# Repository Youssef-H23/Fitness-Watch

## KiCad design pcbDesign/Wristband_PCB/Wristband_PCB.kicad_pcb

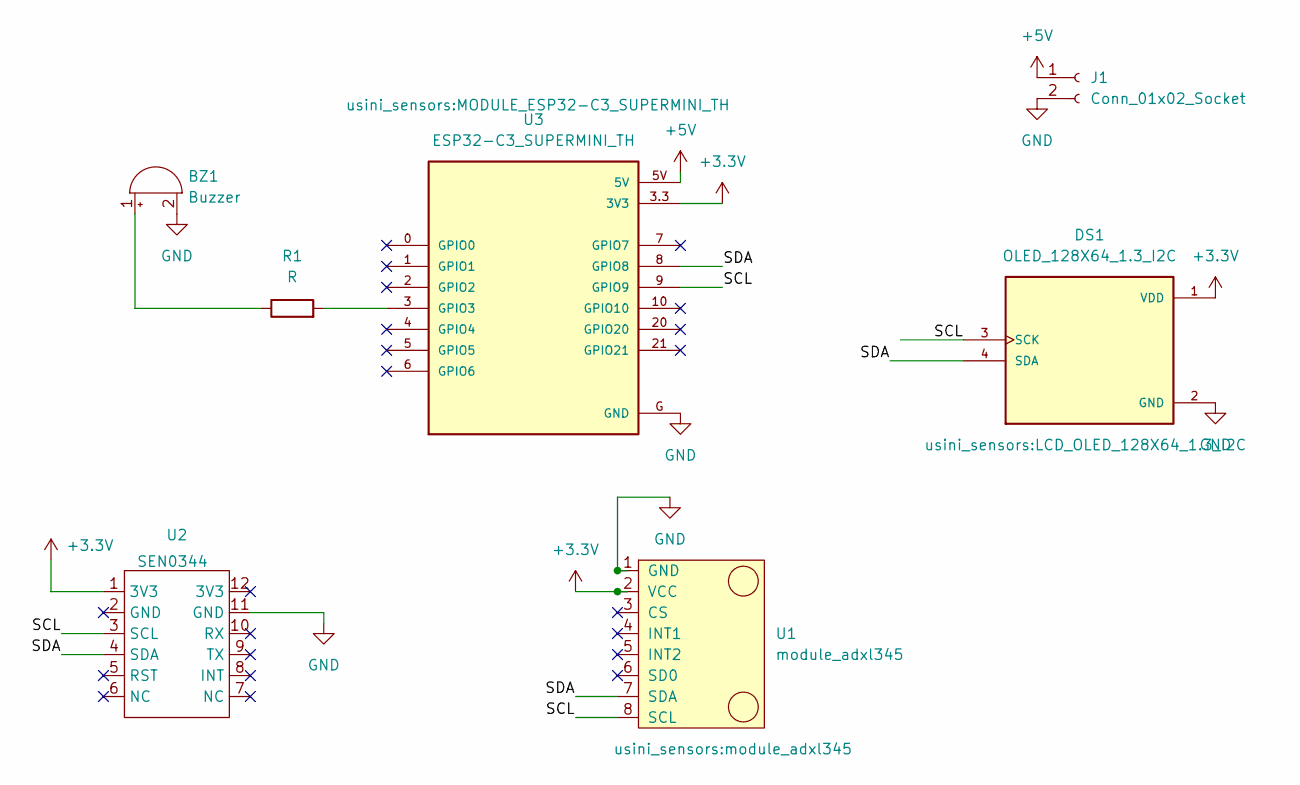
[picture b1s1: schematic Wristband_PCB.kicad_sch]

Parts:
BZ1: Buzzer; Buzzer_12x9.5RM7.6
DS1: OLED_128X64_1.3_I2C; LCD_OLED_128X64_1.3_I2C; PARTREV NA
J1: Conn_01x02_Socket; PinSocket_1x02_P2.54mm_Vertical
R1: R; R_Axial_DIN0204_L3.6mm_D1.6mm_P5.08mm_Horizontal
U1: module_adxl345
U2: SEN0344
U3: ESP32-C3_SUPERMINI_TH; MODULE_ESP32-C3_SUPERMINI_TH

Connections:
+3.3V: DS1.1 (VDD), U1.2 (VCC), U2.1 (3V3), U3.3.3 (3V3)
+5V: J1.1, U3.5V
/SCL: DS1.3 (SCK), U1.8 (SCL), U2.3 (SCL), U3.9 (GPIO9)
/SDA: DS1.4 (SDA), U1.7 (SDA), U2.4 (SDA), U3.8 (GPIO8)
GND: BZ1.2 (-), DS1.2 (GND), J1.2, U1.1 (GND), U2.11 (GND), U3.G (GND)
unnamed: BZ1.1 (+), R1.1
unnamed: R1.2, U3.3 (GPIO3)

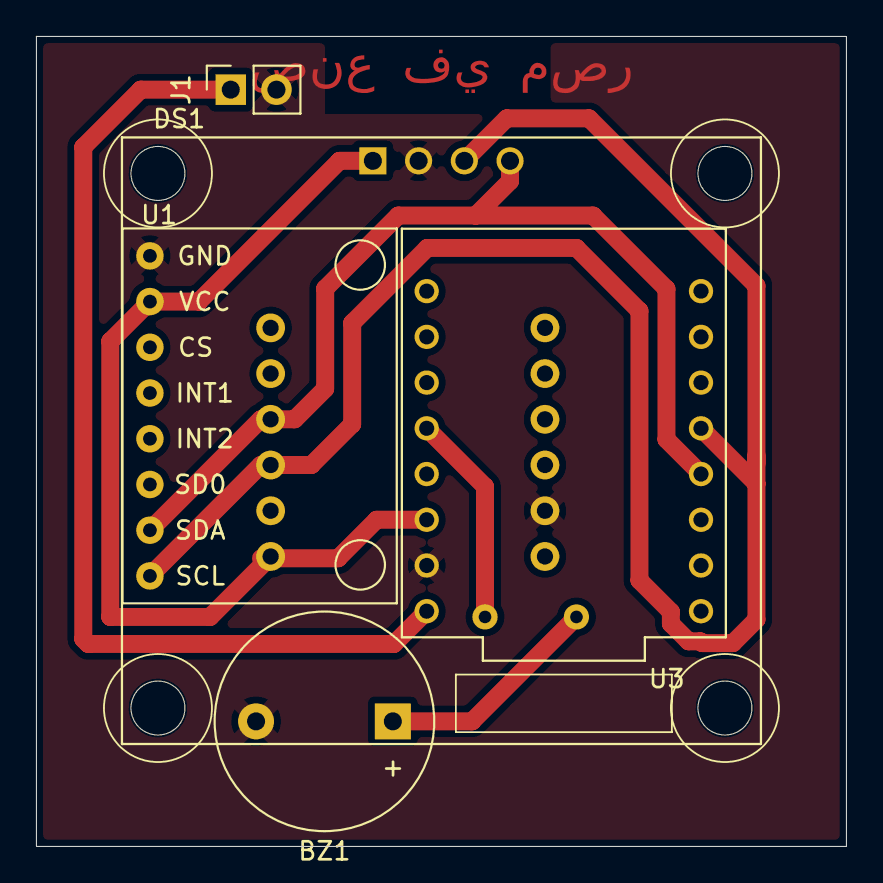
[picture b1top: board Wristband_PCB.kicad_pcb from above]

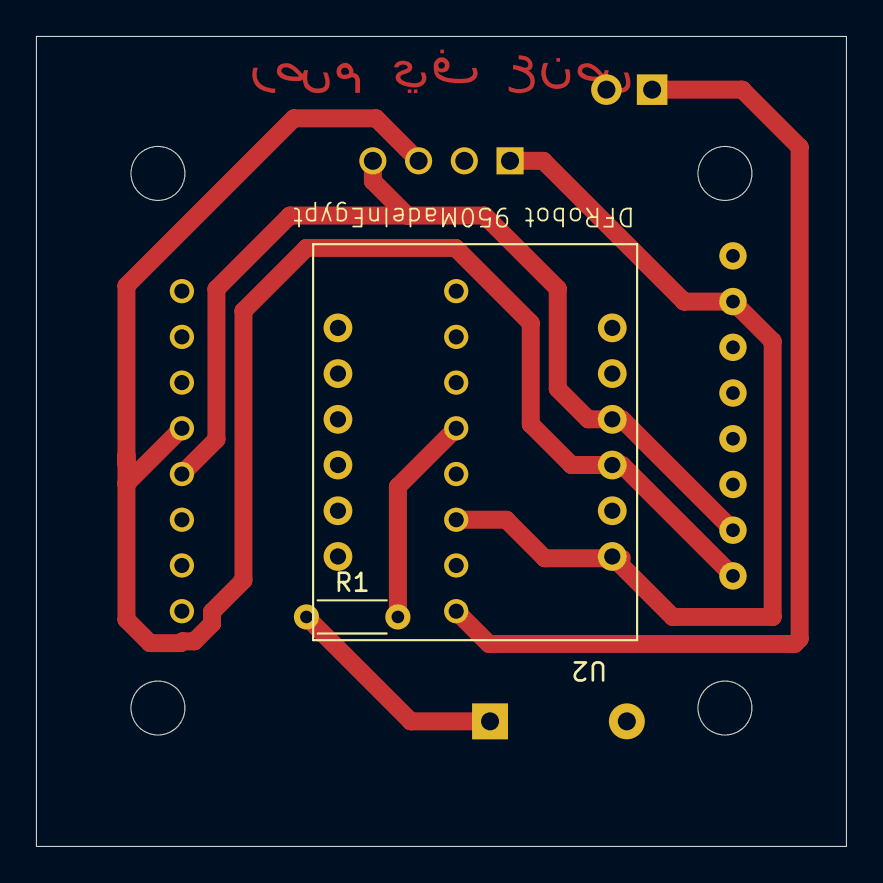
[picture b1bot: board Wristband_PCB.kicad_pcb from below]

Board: 2 copper layers, 45.0 x 45.0 mm, 7 parts (2 on the bottom side), 7 nets.

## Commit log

2026-03-15 adding blutooth
2026-03-20 updated main.ino logic
2026-04-14 updated4 main.ino logic
2026-04-18 Create Node-red
2026-04-18 Rename Node-red to Node_red.json
2026-05-02 pio works
2026-05-04 LCD works formatted nicely random data
2026-05-04 mqtt added but stops when mqtt down
2026-05-04 blocking_calls fixed
2026-05-04 Synchronized time (needs internet)
    1
    1
2026-05-04 adxldata
2026-05-04 maybeworksnow
2026-05-04 works
2026-05-07 gerber-flip
2026-05-09 buzzer added
2026-05-09 added a power socket
2026-05-10 Added print_page.py
2026-05-10 Correct_orientaion
2026-05-10 added the power terminal and the resistor
2026-05-10 removing a not existing lib and makeing path relative
2026-05-12 Update dashboard.json
    add Emergency Alert
